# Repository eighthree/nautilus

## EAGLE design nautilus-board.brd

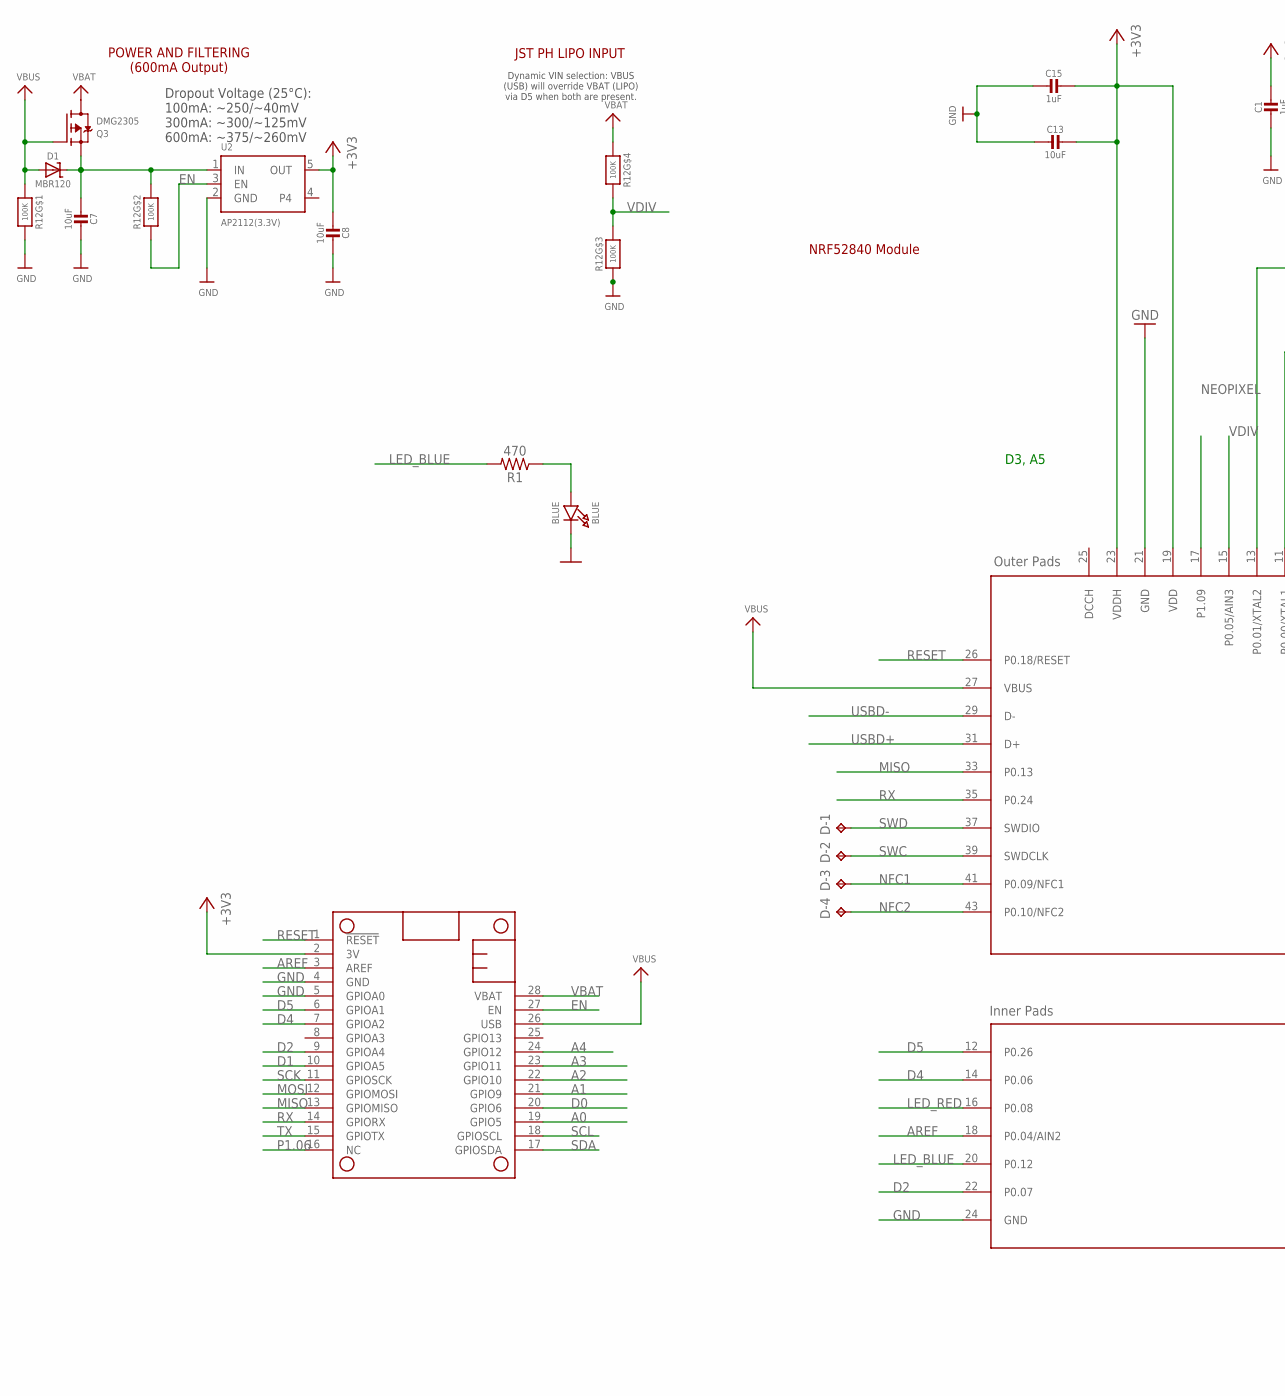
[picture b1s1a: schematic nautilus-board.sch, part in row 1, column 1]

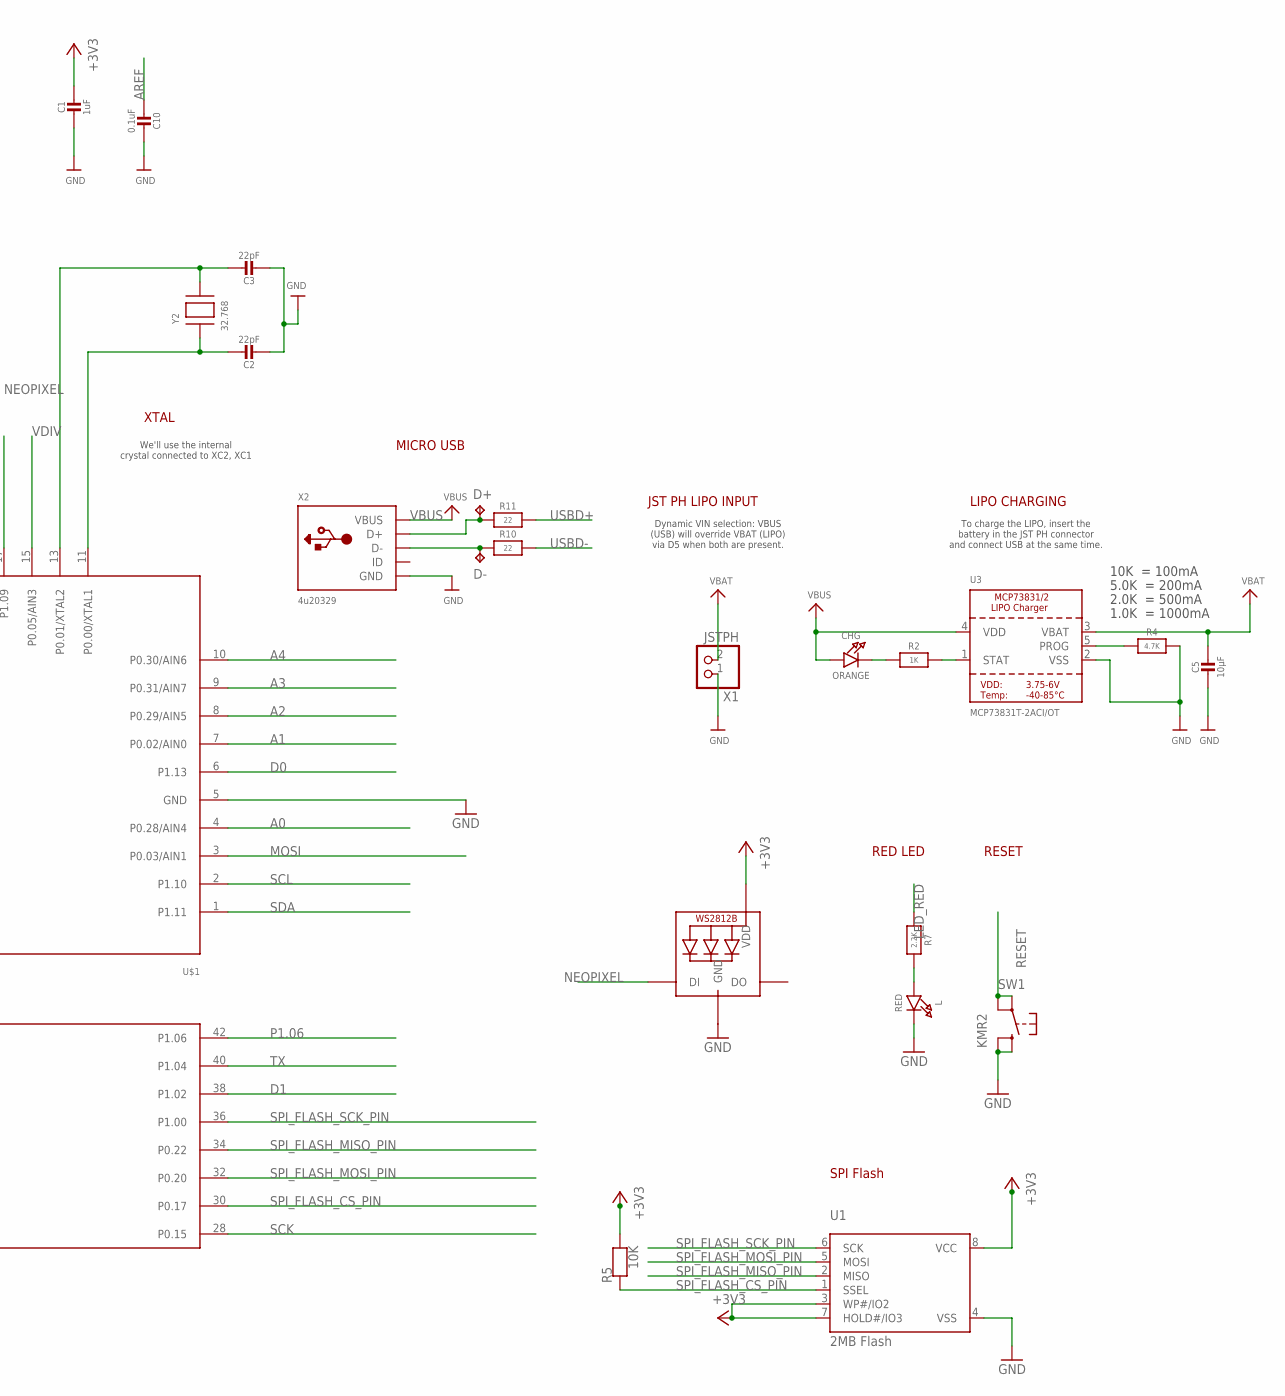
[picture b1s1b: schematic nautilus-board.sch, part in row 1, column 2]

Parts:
BLUE: BLUE; CHIPLED_0805_NOOUTLINE
C1, C15: 1uF; 0603-NO
C2, C3: 22pF; 0603-NO
C5: 10µF; 0805-NO
C7, C8, C13: 10uF; 0805-NO
C10: 0.1uF; 0603-NO
CHG: ORANGE; CHIPLED_0805_NOOUTLINE
D1: MBR120; SOD-123
D+: TPTP10R; TP10R
D-: TPTP10R; TP10R
D-1, D-2, D-3, D-4: TPB1,27; B1,27
L: RED; CHIPLED_0805_NOOUTLINE
LED1: WS2812B3535; LED3535
MS1: FEATHERWING
Q3: DMG2305; SOT23-R
R1: 470; 0603
R2: 1K; 0603-NO
R4: 4.7K; 0603-NO
R5: 10K; 0603-NO
R7: 2.2K; 0603-NO
R10, R11: 22; 0603-NO
R12: 100K; RESPACK_4X0603
SW1: KMR2; BTN_KMR2_4.6X2.8
U1: 2MB Flash; SOIC8_208MIL
U2: AP2112(3.3V); SOT23-5
U3: MCP73831T-2ACI/OT; SOT23-5
U$1: E73-2G4M08S1C; PE73(2G4M08S1C)
X1: JSTPH; JSTPH2
X2: 4u20329; 4UCONN_20329_V2
Y2: 32.768; XTAL3215

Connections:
+3V3: C1.1, C8.2, C13.1, C15.1, LED1.2 (VDD), MS1.2 (3V), R5.2, U1.3 (WP#/IO2), U1.7 (HOLD#/IO3), U1.8 (VCC), U2.5 (OUT), U$1.19 (VDD), U$1.23 (VDDH)
A0: MS1.19 (GPIO5), U$1.4 (P0.28/AIN4)
A1: MS1.21 (GPIO9), U$1.7 (P0.02/AIN0)
A2: MS1.22 (GPIO10), U$1.8 (P0.29/AIN5)
A3: MS1.23 (GPIO11), U$1.9 (P0.31/AIN7)
A4: MS1.24 (GPIO12), U$1.10 (P0.30/AIN6)
AREF: C10.2, MS1.3 (AREF), U$1.18 (P0.04/AIN2)
D0: MS1.20 (GPIO6), U$1.6 (P1.13)
D1: MS1.10 (GPIOA5), U$1.38 (P1.02)
D2: MS1.9 (GPIOA4), U$1.22 (P0.07)
D4: MS1.7 (GPIOA2), U$1.14 (P0.06)
D5: MS1.6 (GPIOA1), U$1.12 (P0.26)
D+1: D+.TP, R11.1, X2.D+
D-1: D-.TP, R10.1, X2.D-
EN: MS1.27 (EN), R12.2 (1), U2.3 (EN)
GND: BLUE.C, C1.2, C2.2, C3.2, C5.2, C7.1, C8.1, C10.1, C13.2, C15.2, L.C, LED1.4 (GND), MS1.4 (GND), MS1.5 (GPIOA0), R4.2, R12.3 (1), R12.8 (2), SW1.B (S), SW1.B' (S1), U1.4 (VSS), U2.2 (GND), U3.2 (VSS), U$1.5 (GND), U$1.21 (GND), U$1.24 (GND), X1.1, X2.BASE@1 (GND), X2.BASE@2 (GND), X2.GND, X2.SPRT@1 (GND), X2.SPRT@2 (GND), X2.SPRT@3 (GND), X2.SPRT@4 (GND)
LED_BLUE: R1.2, U$1.20 (P0.12)
LED_RED: R7.1, U$1.16 (P0.08)
MISO: MS1.13 (GPIOMISO), U$1.33 (P0.13)
MOSI: MS1.12 (GPIOMOSI), U$1.3 (P0.03/AIN1)
unnamed: CHG.C, R2.1
unnamed: C3.1, U$1.13 (P0.01/XTAL2), Y2.P$2
unnamed: L.A, R7.2
unnamed: C2.1, U$1.11 (P0.00/XTAL1), Y2.P$1
unnamed: BLUE.A, R1.1
unnamed: R2.2, U3.1 (STAT)
unnamed: R4.1, U3.5 (PROG)
NEOPIXEL: LED1.1 (DI), U$1.17 (P1.09)
NFC1: D-3.TP, U$1.41 (P0.09/NFC1)
NFC2: D-4.TP, U$1.43 (P0.10/NFC2)
P1.06: MS1.16 (NC), U$1.42 (P1.06)
RESET: MS1.1 (!RESET), SW1.A, SW1.A' (P1), U$1.26 (P0.18/RESET)
RX: MS1.14 (GPIORX), U$1.35 (P0.24)
SCK: MS1.11 (GPIOSCK), U$1.28 (P0.15)
SCL: MS1.18 (GPIOSCL), U$1.2 (P1.10)
SDA: MS1.17 (GPIOSDA), U$1.1 (P1.11)
SPI_FLASH_CS_PIN: R5.1, U1.1 (SSEL), U$1.30 (P0.17)
SPI_FLASH_MISO_PIN: U1.2 (MISO), U$1.34 (P0.22)
SPI_FLASH_MOSI_PIN: U1.5 (MOSI), U$1.32 (P0.20)
SPI_FLASH_SCK_PIN: U1.6 (SCK), U$1.36 (P1.00)
SWC: D-2.TP, U$1.39 (SWDCLK)
SWD: D-1.TP, U$1.37 (SWDIO)
TX: MS1.15 (GPIOTX), U$1.40 (P1.04)
USBD+: R11.2, U$1.31 (D+)
USBD-: R10.2, U$1.29 (D-)
VBAT: C5.1, MS1.28 (VBAT), Q3.3 (D), R12.4 (1), U3.3 (VBAT), X1.2
VBUS: CHG.A, D1.A, MS1.26 (USB), Q3.1 (G), R12.1, U3.4 (VDD), U$1.27 (VBUS), X2.VBUS
VDIV: R12.5 (2), R12.6 (2), U$1.15 (P0.05/AIN3)
VHI: C7.2, D1.C, Q3.2 (S), R12.7 (2), U2.1 (IN)

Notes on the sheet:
NRF52840 Module
JST PH LIPO INPUT
Dynamic VIN selection: VBUS (USB) will override VBAT (LIPO) via D5 when both are present.
10K = 100mA
5.0K = 200mA
2.0K = 500mA
1.0K = 1000mA
LIPO CHARGING
To charge the LIPO, insert the battery in the JST PH connector and connect USB at the same time.
RED LED
RESET
XTAL
We'll use the internal crystal connected to XC2, XC1
MICRO USB
SPI Flash
POWER AND FILTERING (600mA Output)
Dropout Voltage (25°C): 100mA: ~250/~40mV 300mA: ~300/~125mV 600mA: ~375/~260mV
D3, A5

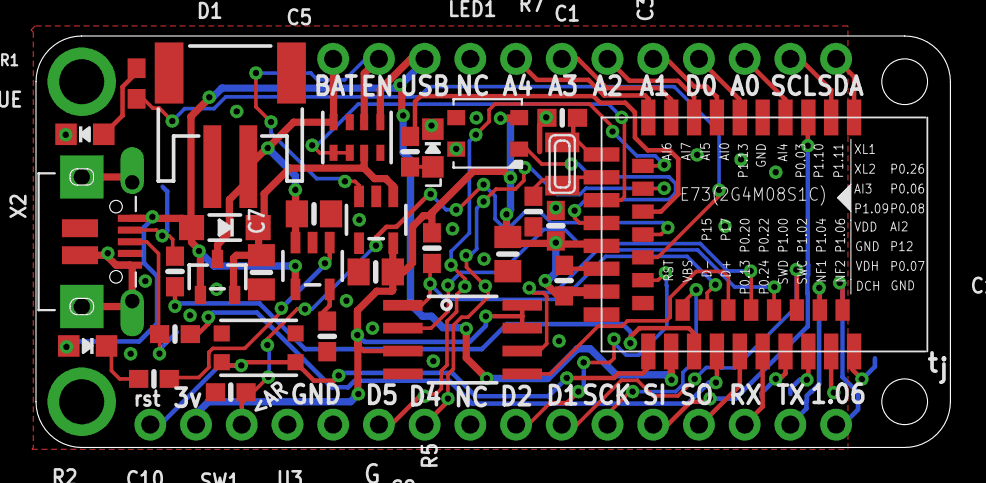
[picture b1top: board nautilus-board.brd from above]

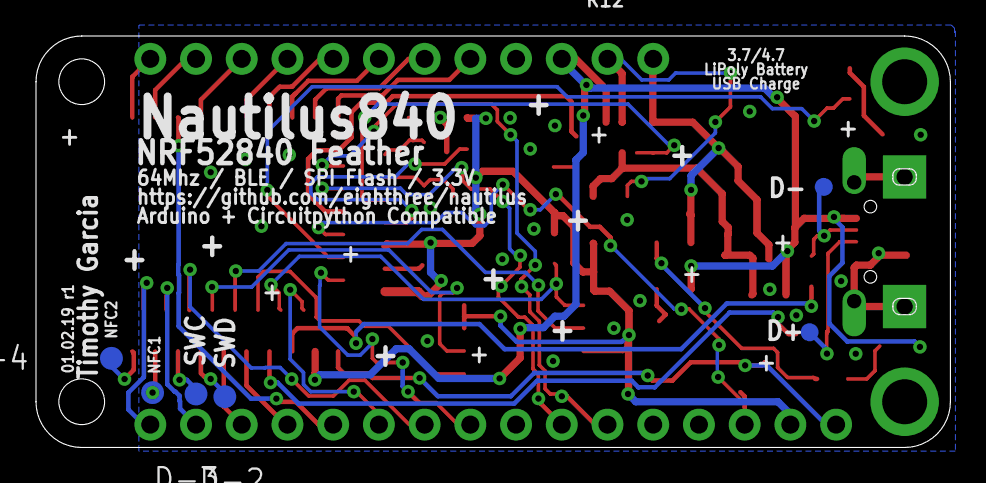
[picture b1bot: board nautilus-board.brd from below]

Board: 2 copper layers, 50.8 x 22.9 mm, 38 parts (6 on the bottom side), 49 nets.

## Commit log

2019-01-03 Initial design
2019-01-03 Silkscreen update
2019-01-03 Adjusted traces
2019-01-03 External XTAL
2019-01-03 Adjustments

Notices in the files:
parts and their libraries:
microbuilder: This work is placed in the public domain, and may be freely used for commercial and non-commercial work with the following conditions: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
SparkFun-Resistors: Licensing: Creative Commons ShareAlike 4.0 International - https://creativecommons.org/licenses/by-sa/4.0
